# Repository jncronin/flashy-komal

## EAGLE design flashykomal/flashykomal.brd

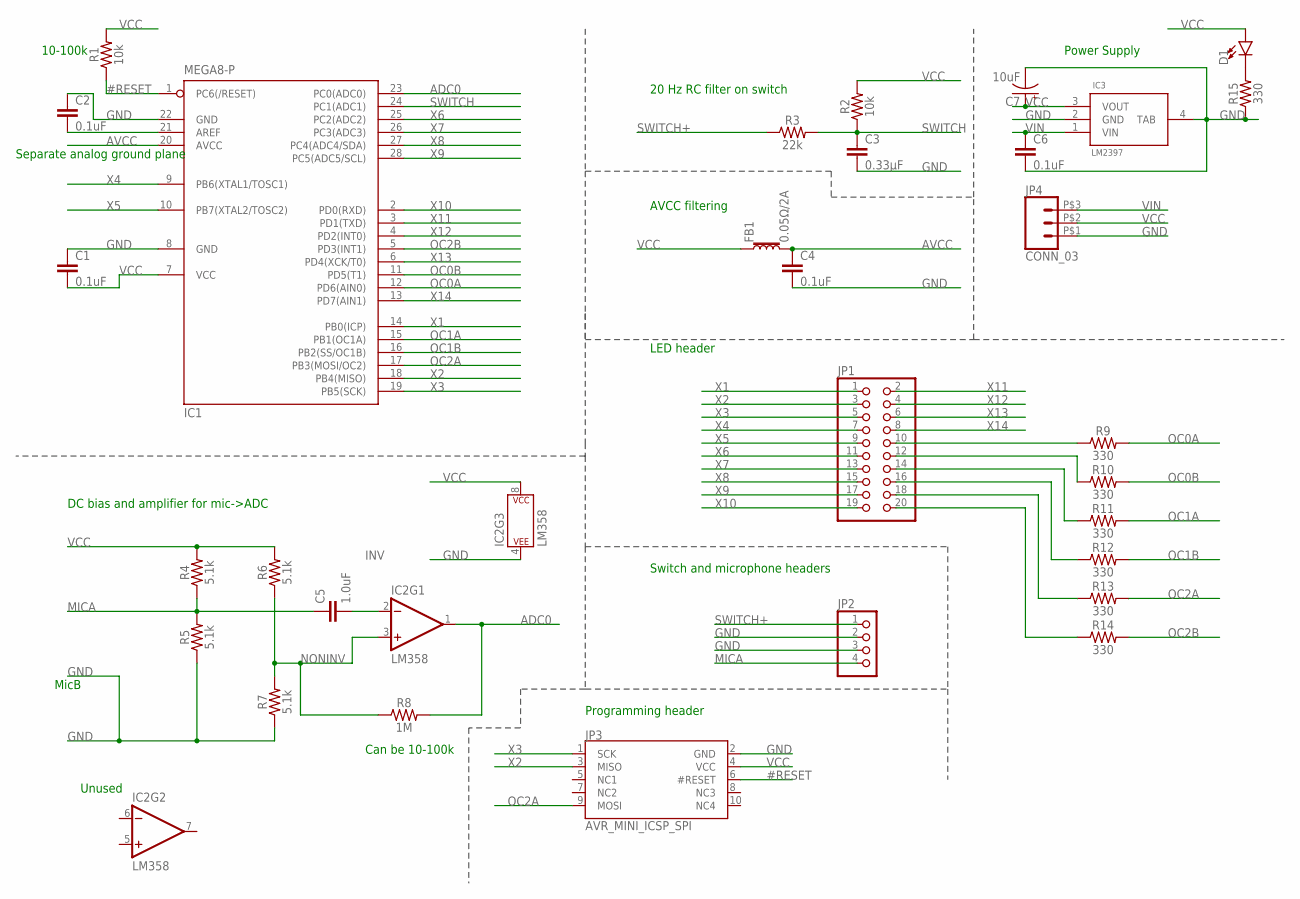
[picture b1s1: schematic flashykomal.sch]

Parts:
C1, C2, C4, C6: 0.1uF; 0603
C3: 0.33µF; 0805
C5: 1.0uF; 0603
C7: 10uF; CPOL-RADIAL-2.5MM-5MM
D1: LED0603; LED-0603
FB1: 0.05Ω/2A; 0603
IC1: MEGA8-P; DIL28-3
IC2: LM358; DIP08
IC3: LM2397; SOT223
JP1: PINHD-2X10; 2X10
JP2: PINHD-1X4; 1X04
JP3: AVR_MINI_ICSP_SPI; SAMTECH_FTSH-105-01
JP4: CONN_03; PH1X3-381
R1, R2: 10k; 0603
R3: 22k; 0603
R4, R5, R6, R7: 5.1k; 0603
R8: 1M; 0603
R9, R10, R11, R12, R13, R14, R15: 330; 0603

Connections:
#RESET: IC1.1 (PC6(/RESET)), JP3.6 (#RESET), R1.1
ADC0: IC1.23 (PC0(ADC0)), IC2.1 (OUT), R8.2
AVCC: C4.1, FB1.2, IC1.20 (AVCC)
GND: C1.1, C2.1, C3.2, C4.2, C6.2, C7.2 (-), IC1.8 (GND), IC1.22 (GND), IC2.4 (P$V-), IC3.2 (GND), IC3.4 (TAB), JP2.2, JP2.3, JP3.2 (GND), JP4.P$1 (1), R5.1, R7.1, R15.1
INV: C5.2, IC2.2 (-IN)
MICA: C5.1, JP2.4, R4.1, R5.2
unnamed: D1.C, R15.2
unnamed: C2.2, IC1.21 (AREF)
unnamed: JP1.10, R9.1
unnamed: JP1.12, R10.1
unnamed: JP1.14, R11.1
unnamed: JP1.16, R12.1
unnamed: JP1.18, R13.1
unnamed: JP1.20, R14.1
NONINV: IC2.3 (+IN), R6.1, R7.2, R8.1
OC0A: IC1.12 (PD6(AIN0)), R9.2
OC0B: IC1.11 (PD5(T1)), R10.2
OC1A: IC1.15 (PB1(OC1A)), R11.2
OC1B: IC1.16 (PB2(SS/OC1B)), R12.2
OC2A: IC1.17 (PB3(MOSI/OC2)), JP3.9 (MOSI), R13.2
OC2B: IC1.5 (PD3(INT1)), R14.2
SWITCH: C3.1, IC1.24 (PC1(ADC1)), R2.1, R3.2
SWITCH+: JP2.1, R3.1
VCC: C1.2, C7.1 (+), D1.A, FB1.1, IC1.7 (VCC), IC2.8 (P$V+), IC3.3 (VOUT), JP3.4 (VCC), JP4.P$2 (2), R1.2, R2.2, R4.2, R6.2
VIN: C6.1, IC3.1 (VIN), JP4.P$3 (3)
X1: IC1.14 (PB0(ICP)), JP1.1
X2: IC1.18 (PB4(MISO)), JP1.3, JP3.3 (MISO)
X3: IC1.19 (PB5(SCK)), JP1.5, JP3.1 (SCK)
X4: IC1.9 (PB6(XTAL1/TOSC1)), JP1.7
X5: IC1.10 (PB7(XTAL2/TOSC2)), JP1.9
X6: IC1.25 (PC2(ADC2)), JP1.11
X7: IC1.26 (PC3(ADC3)), JP1.13
X8: IC1.27 (PC4(ADC4/SDA)), JP1.15
X9: IC1.28 (PC5(ADC5/SCL)), JP1.17
X10: IC1.2 (PD0(RXD)), JP1.19
X11: IC1.3 (PD1(TXD)), JP1.2
X12: IC1.4 (PD2(INT0)), JP1.4
X13: IC1.6 (PD4(XCK/T0)), JP1.6
X14: IC1.13 (PD7(AIN1)), JP1.8

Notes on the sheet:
10-100k
Separate analog ground plane
20 Hz RC filter on switch
DC bias and amplifier for mic->ADC
AVCC filtering
MicB
Unused
Can be 10-100k
LED header
Switch and microphone headers
Power Supply
Programming header

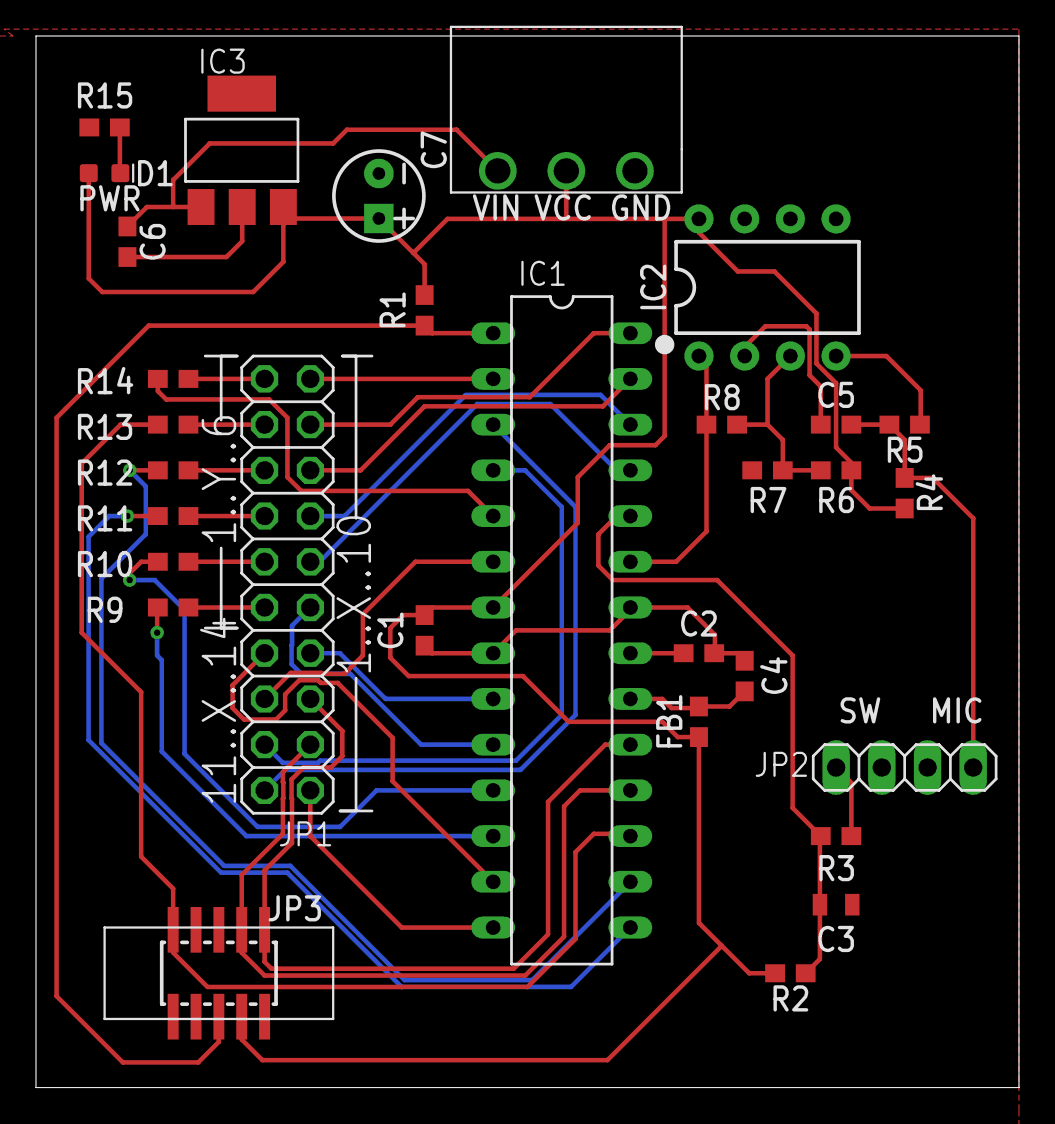
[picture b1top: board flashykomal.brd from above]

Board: 2 copper layers, 54.6 x 58.4 mm, 31 parts (0 on the bottom side), 39 nets.

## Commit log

2019-09-02 Add JP1 markings
2019-09-02 Power LED

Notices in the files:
parts and their libraries:
SparkFun-Capacitors: Licensing: Creative Commons ShareAlike 4.0 International - https://creativecommons.org/licenses/by-sa/4.0
